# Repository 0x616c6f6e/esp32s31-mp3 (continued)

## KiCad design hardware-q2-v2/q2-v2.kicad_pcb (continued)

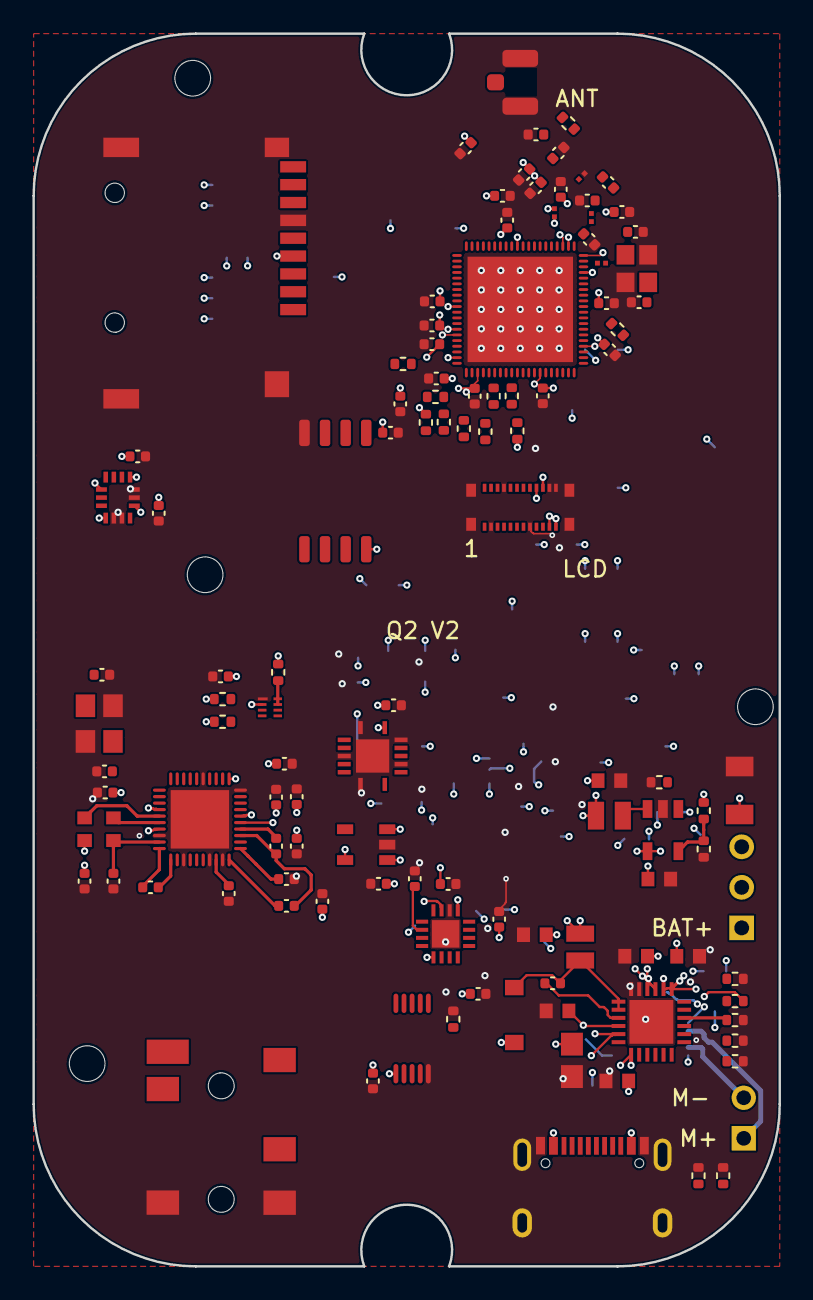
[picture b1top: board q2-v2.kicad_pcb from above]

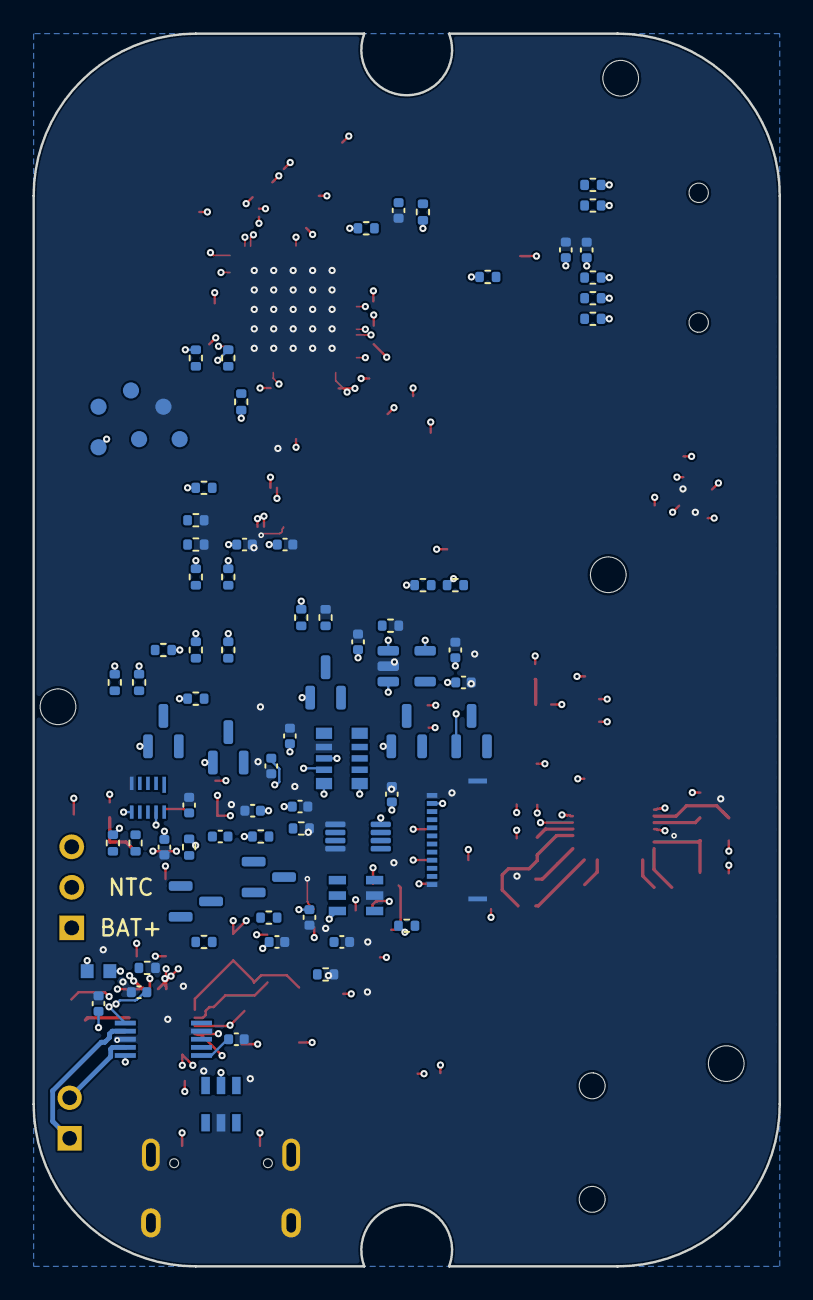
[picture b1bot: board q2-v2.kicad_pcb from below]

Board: 6 copper layers, 46.0 x 76.0 mm, 198 parts (83 on the bottom side), 144 nets.

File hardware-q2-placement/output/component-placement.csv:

Reference,Side,X_mm,Y_mm,Rotation_deg,Value,Locked
C1,B,126.25,90.25,0.0,10uF,False
C10,B,135.5,108.25,0.0,10uF,False
C11,B,144.25,111.25,90.0,47nF,False
C12,B,141.75,107.75,-90.0,10uF,False
C14,B,135.5,116.75,90.0,1uF,False
C15,B,133.5,110.25,0.0,10uF,False
C16,B,138.75,116.25,180.0,47uF,False
C17,F,106.5,108.25,180.0,2.2uF,False
C18,F,106.0,106.5,180.0,22uF,False
C19,F,103.5,106.0,90.0,2.2uF,False
C2,B,129.5,88.0,0.0,10uF,False
C20,F,109.5,109.75,0.0,2.2uF,False
C21,F,116.25,110.5,-90.0,2.2uF,False
C22,F,111.75,110.5,-90.0,2.2uF,False
C23,F,115.75,104.5,-90.0,2.2uF,False
C24,F,115.75,107.25,-90.0,2.2uF,False
C25,F,114.0,109.75,0.0,2.2uF,False
C26,F,117.25,105.0,90.0,4.7uF,False
C27,F,115.5,101.5,0.0,100nF,False
C28,B,108.5,105.0,0.0,100nF,False
C29,F,117.25,107.75,-90.0,100nF,False
C3,B,115.75,88.0,180.0,100nF,False
C30,F,124.0,99.0,90.0,1uF,False
C31,F,118.0,100.0,-90.0,1uF,False
C32,F,114.75,99.0,-90.0,10pF,False
C33,F,108.5,100.0,90.0,10pF,False
C34,F,105.5,95.25,-90.0,100nF,False
C35,F,118.25,90.75,180.0,100nF,False
C36,B,138.25,104.0,0.0,100nF,False
C37,B,133.75,93.75,-90.0,100nF,False
C38,B,131.25,97.0,0.0,100nF,False
C39,F,121.019,66.581,-90.0,1uF,False
C4,F,120.25,117.25,-90.0,1uF,False
C40,F,121.019,63.914,90.0,100nF,False
C41,F,119.749,63.914,90.0,1uF,False
C42,B,135.5,75.5,90.0,10uF,False
C43,B,139.75,99.25,90.0,220nF,False
C44,B,127.5,96.0,-90.0,100nF,False
C45,B,143.323,66.018,0.0,100nF,False
C46,B,137.608,62.081,0.0,100nF,False
C47,F,120.5,78.5,0.0,100nF,False
C48,F,115.25,78.0,-90.0,100nF,False
C49,B,119.574,63.935,-90.0,10uF,False
C5,F,120.25,113.75,90.0,1uF,False
C50,B,120.8615,63.93,-90.0,100nF,False
C53,F,140.0,92.5,-90.0,100nF,False
C54,F,138.5,92.5,-90.0,1uF,False
C55,B,131.0,75.75,90.0,10uF,False
C56,B,138.5,78.25,180.0,10uF,False
C57,B,138.25,76.25,180.0,10uF,False
C58,F,121.5,111.25,0.0,100nF,False
C6,F,141.75,86.5,90.0,100nF,False
C7,F,143.25,88.0,-90.0,100nF,False
C8,F,106.0,104.5,180.0,22uF,False
C9,B,142.75,115.75,0.0,4.7uF,False
CARD2,F,111.7,65.764,-90.0,TF PUSH,True
CN1,F,112.565,118.425,90.0,PJ-342B-TX-SMT,True
D1,F,135.5,115.75,0.0,USBLC6-2SC6,False
D2,B,142.25,112.25,90.0,B5817W,False
FPC2,B,140.148,69.4,90.0,2.09寸320*375高清R角方屏QSPI,True
H1,F,130.0,113.0,-90.0,BM02B-ACHSS-GAN-ETF,True
H2,F,142.0,109.0,-90.0,BM03B-ACHSS-GAN-ETF,True
L1,B,129.75,85.75,180.0,2.2uH,False
L2,B,139.0,108.0,0.0,2.2uH,False
L3,F,124.5,111.0,0.0,BLM18KG601SN1D,False
L4,B,133.25,75.75,-90.0,4.7uH,False
R1,B,144.0,106.5,90.0,10mΩ,False
R11,B,132.25,114.75,90.0,100K,False
R12,B,133.75,117.0,90.0,100K,False
R13,B,133.0,112.5,90.0,5K23,False
R14,B,131.0,110.25,-90.0,30K1,False
R17,F,109.0,92.5,90.0,200K,False
R18,F,107.0,93.0,180.0,10K,False
R19,F,104.0,95.25,90.0,10K,False
R2,B,141.0,103.5,180.0,1K,False
R20,B,141.594,62.85,0.0,10K,False
R21,B,139.25,97.25,180.0,100K,False
R22,B,136.0,104.0,180.0,100K,False
R25,B,141.594,64.376,0.0,10K,False
R26,F,109.25,94.75,-90.0,10K,False
R27,B,130.25,91.0,0.0,0/NC,False
R28,B,127.5,93.75,90.0,0/NC,False
R29,F,119.749,66.454,90.0,10K,False
R3,B,123.25,90.0,90.0,22K1,False
R30,F,109.75,96.75,180.0,10K,False
R31,F,132.25,117.75,0.0,5K1,False
R32,F,138.75,117.75,180.0,5K1,False
R33,B,139.75,101.5,90.0,1K,False
R34,B,141.5,105.0,180.0,0R/NC,False
R35,B,120.209,60.303,0.0,10K,False
R36,B,120.209,68.177,0.0,10K,False
R37,B,120.209,66.907,0.0,10K,False
R38,B,120.209,61.573,0.0,10K,False
R39,B,120.209,65.637,0.0,10K,False
R4,B,123.25,87.75,90.0,100K,False
R40,B,139.5,80.5,180.0,1R5,False
R41,B,131.5,81.0,90.0,100K,False
R42,F,141.75,91.25,90.0,10K,False
R43,B,133.75,114.75,90.0,10K,False
R44,F,125.75,117.5,-90.0,10K,False
R5,B,125.5,84.0,180.0,100K,False
R7,F,135.75,88.0,-90.0,10K,False
R8,F,141.75,88.75,90.0,10K,False
R9,B,134.5,112.5,90.0,700R,False
SCREW1,F,104.3,114.5,0.0,M2 clearance 2.2mm,True
SCREW2,F,111.573,84.3608,0.0,M2 clearance 2.2mm,True
SCREW4,F,145.5,92.5,0.0,M2 clearance 2.2mm,True
SCREW5,F,110.8085,53.7485,0.0,M2 clearance 2.2mm,True
U1,F,139.0,89.0,0.0,RX8130CE:BB,False
U11,F,123.0,115.5,0.0,DRV2605LDGSR,False
U12,B,130.5,94.0,-90.0,CH343P,False
U14,B,142.5,101.0,0.0,STC3115AIQT,False
U15,F,117.7,78.0,90.0,LSM6DS3TR-C,False
U16,B,134.56,79.559,180.0,PAM2804AAB010,False
U17,B,136.0,100.0,180.0,SGM7229YMS10G/TR,False
U2,F,111.7,105.69,0.0,CS43131-CNZ,False
U3,B,138.0,112.2,90.0,DSCB_BQ25895RTW,False
U4,B,126.0,87.0,90.0,TLV62568DBVR,False
U5,F,121.0,99.5,0.0,ME6211C18M5G-N,False
U6,B,116.5,91.0,-90.0,GEK100,False
U7,F,107.4,95.0,-90.0,PCA9306DQER,False
U8,F,117.0,94.0,-90.0,SN74LV4T125RGYR,False
U9,F,133.719,72.931,0.0,ESP32-S31-WROOM-3-N16R16V,True
USB1,F,135.449,121.946,0.0,TYPE-C 16PIN 2MD(073),True
X1,F,111.5,100.25,180.0,26MHz,False

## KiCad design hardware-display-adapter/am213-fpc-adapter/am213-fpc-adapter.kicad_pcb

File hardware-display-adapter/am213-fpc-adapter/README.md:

# AM213 转接板 A

打开 `am213-fpc-adapter.kicad_pro`。现为已完成原理图和布线的电气工程，取代旧机械占位版本。

- 原理图、PCB：同名 `.kicad_sch`、`.kicad_pcb`
- 自带库：`Adapter.kicad_sym`、`Adapter.pretty`、`models3d`
- 最新装配副本：`models3d/Q2_L_AM213_Completed_Adapter.FCStd`
- 检查、BOM、预览及制造审核包：`output/`

采用屏厂 3.3 V 直接接线参考；17×22 mm 元件岛、70 mm 左出尾巴；J2 局部 **(3,12)**、1 脚左上。R10/R11 不装。ERC/DRC、未连接和原理图一致性问题均为 0。

详见[接线与坐标](../fpc-layout-guide.md)、[电气依据](../README.md)、[制造说明](FABRICATION.md)。先审核柔性叠层、补强、0.15 mm 小孔及金手指工艺，再做样板；尚未实物插合和点亮。

`Adapter_Placement.pretty`、旧 `placement-preview.*` 及 `models3d/Q2_L_BTB_Fit_Review.FCStd` 为历史阶段文件。

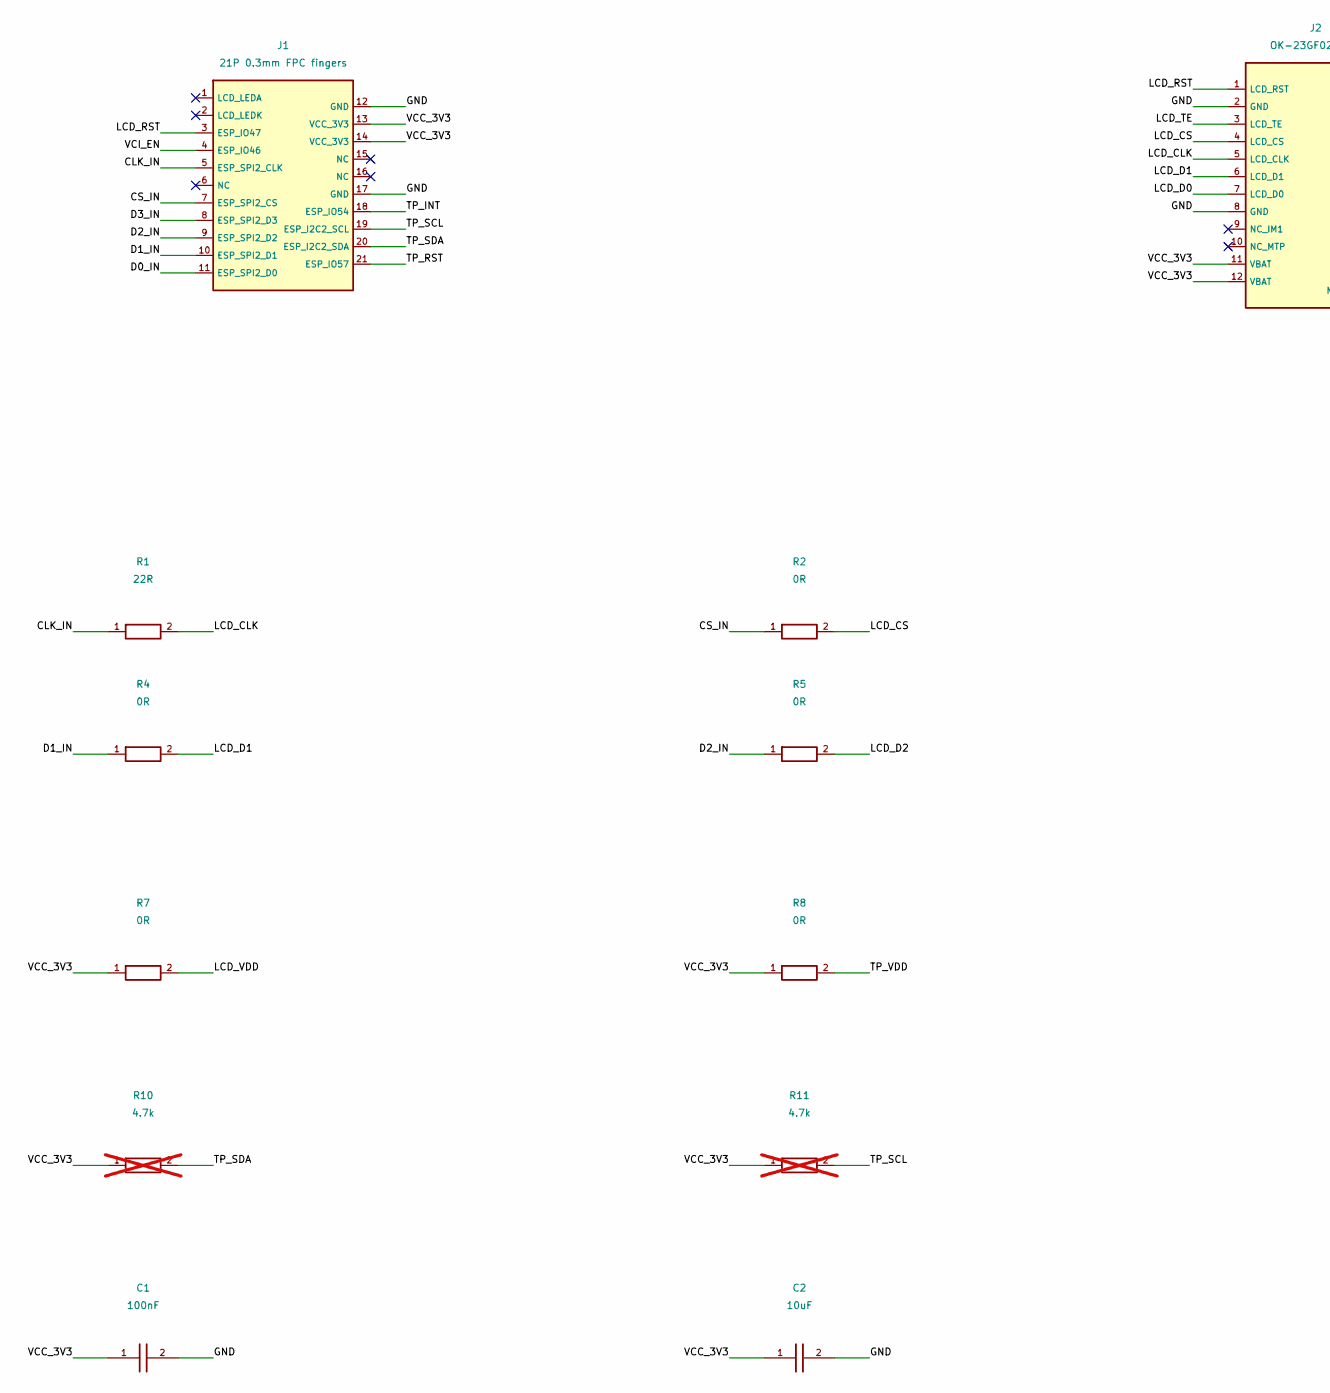
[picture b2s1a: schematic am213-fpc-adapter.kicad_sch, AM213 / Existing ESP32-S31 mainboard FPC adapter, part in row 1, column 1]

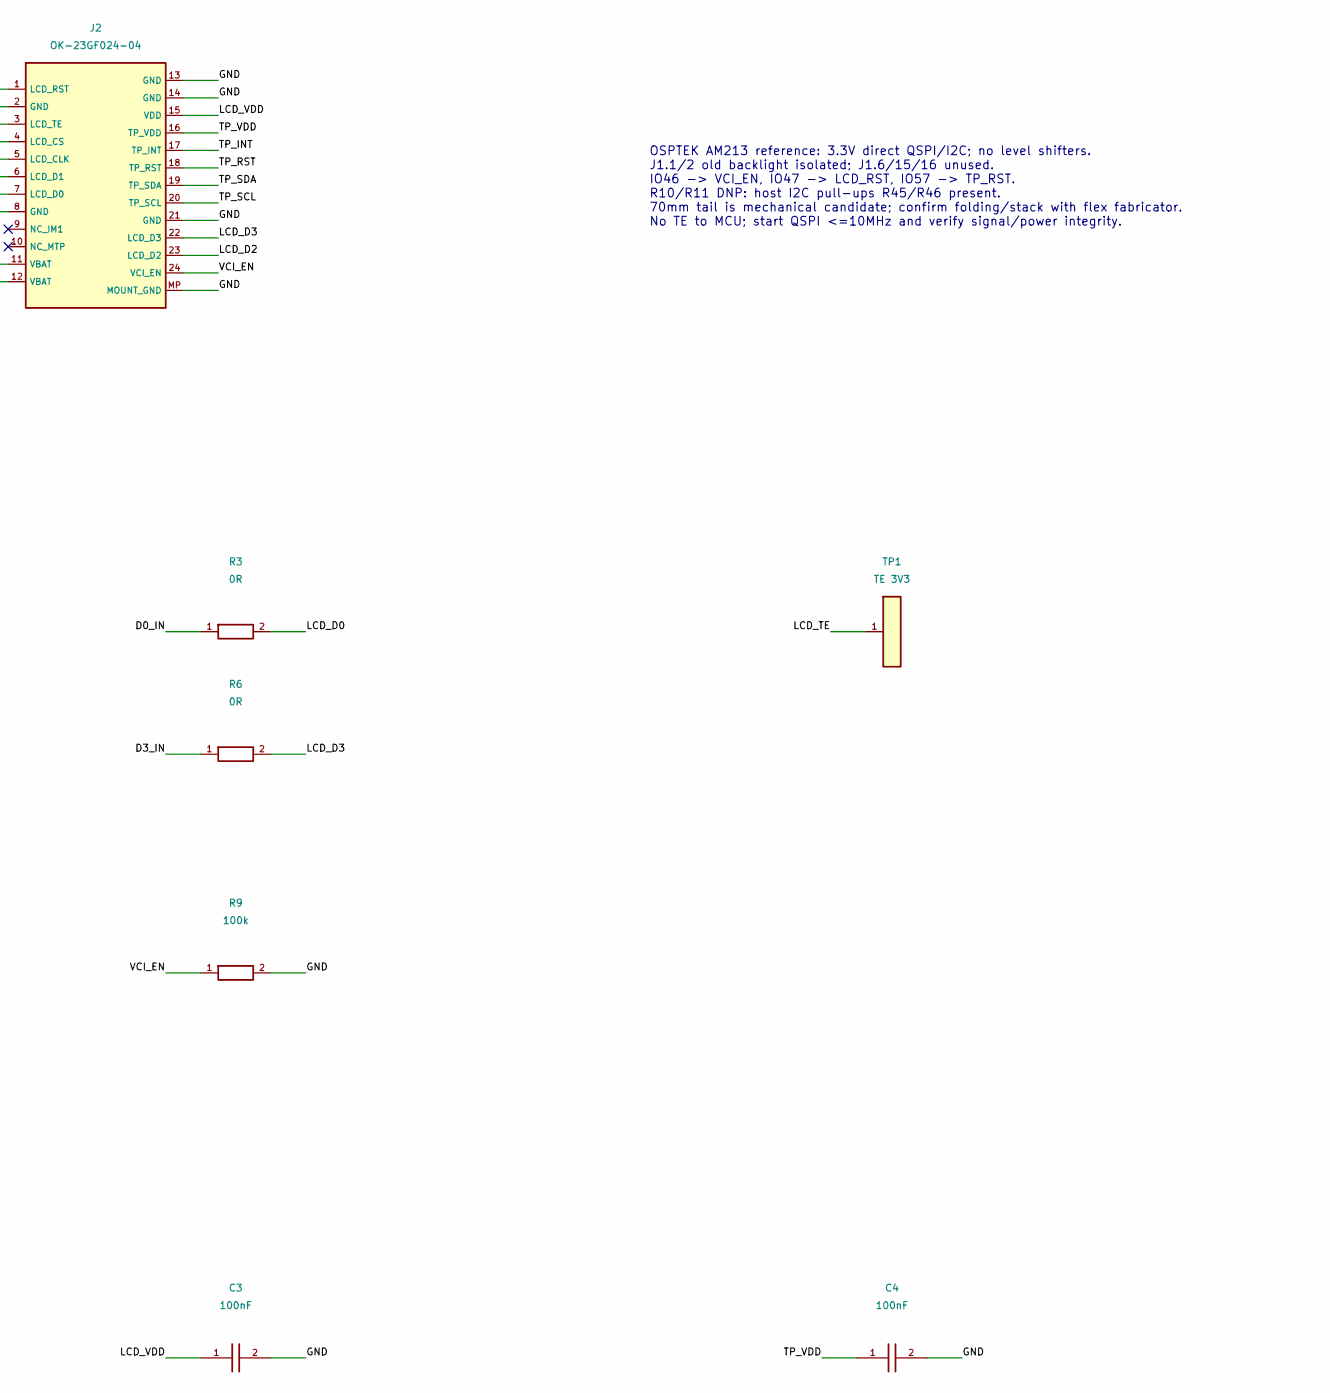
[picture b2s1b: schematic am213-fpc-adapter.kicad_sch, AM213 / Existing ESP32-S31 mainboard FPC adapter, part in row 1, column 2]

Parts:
C1, C3, C4: 100nF; C0402
C2: 10uF; C0603
J1: 21P 0.3mm FPC fingers; FPC21_Fingers
J2: OK-23GF024-04; OK23GF024
R1: 22R; R0402
R2, R3, R4, R5, R6, R7, R8: 0R; R0402
R9: 100k; R0402
R10, R11: 4.7k; R0402; not fitted
TP1: TE 3V3; TP

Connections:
/CLK_IN: J1.5 (ESP_SPI2_CLK), R1.1
/CS_IN: J1.7 (ESP_SPI2_CS), R2.1
/D0_IN: J1.11 (ESP_SPI2_D0), R3.1
/D1_IN: J1.10 (ESP_SPI2_D1), R4.1
/D2_IN: J1.9 (ESP_SPI2_D2), R5.1
/D3_IN: J1.8 (ESP_SPI2_D3), R6.1
/GND: C1.2, C2.2, C3.2, C4.2, J1.12 (GND), J1.17 (GND), J2.2 (GND), J2.8 (GND), J2.13 (GND), J2.14 (GND), J2.21 (GND), J2.MP (MOUNT_GND), R9.2
/LCD_CLK: J2.5 (LCD_CLK), R1.2
/LCD_CS: J2.4 (LCD_CS), R2.2
/LCD_D0: J2.7 (LCD_D0), R3.2
/LCD_D1: J2.6 (LCD_D1), R4.2
/LCD_D2: J2.23 (LCD_D2), R5.2
/LCD_D3: J2.22 (LCD_D3), R6.2
/LCD_RST: J1.3 (ESP_IO47), J2.1 (LCD_RST)
/LCD_TE: J2.3 (LCD_TE), TP1.1
/LCD_VDD: C3.1, J2.15 (VDD), R7.2
/TP_INT: J1.18 (ESP_IO54), J2.17 (TP_INT)
/TP_RST: J1.21 (ESP_IO57), J2.18 (TP_RST)
/TP_SCL: J1.19 (ESP_I2C2_SCL), J2.20 (TP_SCL), R11.2
/TP_SDA: J1.20 (ESP_I2C2_SDA), J2.19 (TP_SDA), R10.2
/TP_VDD: C4.1, J2.16 (TP_VDD), R8.2
/VCC_3V3: C1.1, C2.1, J1.13 (VCC_3V3), J1.14 (VCC_3V3), J2.11 (VBAT), J2.12 (VBAT), R7.1, R8.1, R10.1, R11.1
/VCI_EN: J1.4 (ESP_IO46), J2.24 (VCI_EN), R9.1

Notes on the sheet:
OSPTEK AM213 reference: 3.3V direct QSPI/I2C; no level shifters. J1.1/2 old backlight isolated; J1.6/15/16 unused. IO46 -> VCI_EN, IO47 -> LCD_RST, IO57 -> TP_RST. R10/R11 DNP: host I2C pull-ups R45/R46 present. 70mm tail is mechanical candidate; confirm folding/stack with flex fabricator. No TE to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

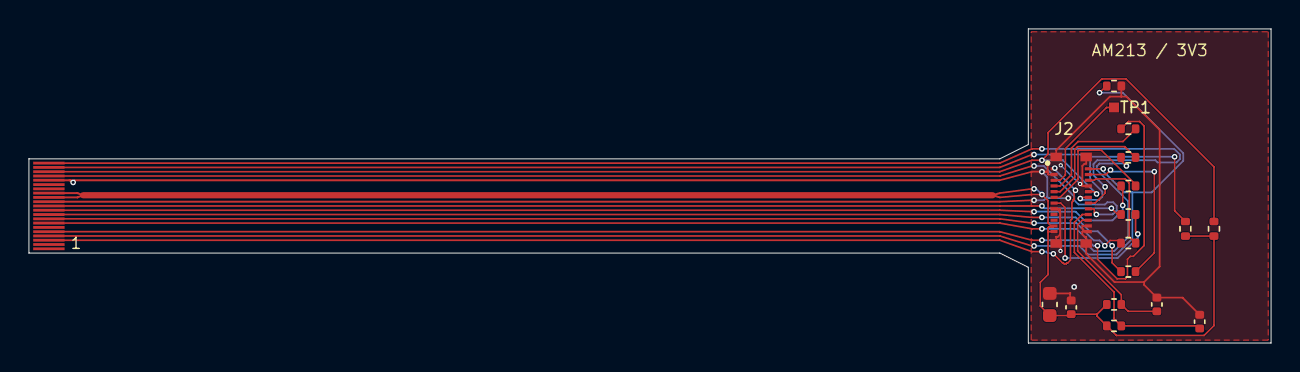
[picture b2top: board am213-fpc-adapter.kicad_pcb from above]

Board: 2 copper layers, 87.0 x 22.0 mm, 18 parts (0 on the bottom side), 23 nets.

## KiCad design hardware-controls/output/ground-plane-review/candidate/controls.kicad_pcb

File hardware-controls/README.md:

# 滑环与按键小板 C：CH32V006

采用 **CH32V006F8U6** 替换 AT42QT2120-MMHR 和 TCA6408A，由一颗 MCU 处理三电极滑环、四个机械按键，并作为 I²C 从机向主板报告。POWER 保持独立、10 kΩ 上拉、按下接地。

这是需要配套固件和实物调参的新硬件版本，不能直接沿用旧 AT42 的驱动或生产文件。

KiCad 10.0.4 检查结果：ERC 0、DRC 0、未连接项 0、原理图一致性问题 0。板上共有 439 段走线和 62 个过孔。双面 GND 铺铜避开触摸电极及其背面（外扩约 0.8 mm），并避开三路采样走线（铜边外扩约 0.5 mm）；这些余量仍需实物验证。

新版文件：[Gerber 生产包](output/controls-ch32v006-jlcpcb-20260922-101316-gerbers.zip)、[BOM](output/controls-ch32v006-bom.csv)、[装配 STEP](output/controls-ch32v006.step)、[背面预览](output/ch32v006-review/back.png)。BOM 由当前原理图导出，共 10 类、23 个装配元件，尚未匹配嘉立创 SMT 料号。

## 工程与机械接口

- KiCad 工程：`controls.kicad_pro`，原理图、PCB、本地符号库、封装库与模型一起使用。
- 双层 FR-4，板厚 0.8 mm，44 × 34 mm，原 R10 板框。
- 五个按键、四个安装孔、三电极滑环 E1、FPC J1 的位置与方向保持原样。
- 电极仍为三组插值电极，外径 31 mm、内径 15 mm；不改变前面板外观。
- 新 MCU 及阻容位于背面。J2 为四个裸焊盘，不安装插针，不增加连接器高度。
- 已添加名义尺寸的 CH32V006 QFN20 STEP 模型。本版 23 个元件已导入 [I 版装配优化工程](../mechanical/enclosure-final-i/README.md)，最新工程为 `mechanical/enclosure-final-i/Q2_I_Serviceable_Assembly.FCStd`。小板采用三颗 M1.6 × 2 mm（头下长度）薄头螺钉、三片 0.3 mm 平垫及右侧限位台；右上原固定柱封闭不装螺钉，避开 FFC。G/H 复合实体检查曾漏报该处干涉，使用 I 版检查和打印文件。

J1：1 GND、2 +3V3、3 SDA、4 SCL、5 INT_N、6 RESET_N、7～10 NC、11 KEY_POWER、12 GND；固定焊盘 13、14 接地。供电与信号电平为 3.3 V。

## 采购与装配变化

| 位号 | C 版器件/数值 | 数量 | 说明 |
|---|---|---:|---|
| U1 | CH32V006F8U6 | 1 | QFN20，3×3 mm，0.4 mm 脚距，EP 1.9×1.9 mm |
| J1 | HC-FPC-05-10-12RLTAG | 1 | 原 12 pin、0.5 mm FPC 连接器 |
| SW1～SW5 | SKSWCEE010 | 5 | 原机械开关 |
| R1～R3 | 1 kΩ，0402 | 3 | 触摸采样串阻，需实物调参 |
| R4、R5 | 4.7 kΩ，0402 | 2 | I²C 上拉 |
| R6、R7、R14 | 10 kΩ，0402 | 3 | INT、RESET、POWER 上拉 |
| R8 | 0 Ω，0402 | 1 | MCU 电源连接，不能装旧 22 Ω |
| R9～R12 | 47 kΩ，0402 | 4 | 四个普通键的 GPIO 上拉 |
| C1、C3 | 100 nF，0402，X7R，≥10 V | 2 | MCU 去耦、复位 RC |
| C2 | 1 µF，0402，X5R/X7R，≥10 V | 1 | MCU 电源去耦 |

单板 23 个采购/装配元件。J2、E1、H1～H4 为 PCB 自带焊盘、电极及安装孔，不采购。U2、R13、C4 已移除；C3 现在用于复位，不能按旧版位置和功能装配。型号后缀及封装必须核对，TSSOP20 的 CH32V006F8P6 不能替代此 QFN20 焊盘。

## 固件

见 [CH32V006-interface.md](CH32V006-interface.md)：完整引脚分配、SDI 下载、PD7 硬件复位配置，以及拟定的 I²C 寄存器协议。地址暂定 0x1C，寄存器与 AT42QT2120 不兼容。本次没有交付可烧录固件；官方 TouchKey 示例也不能原样烧录到此板。

打样后要在最终盖板下标定三路触摸基线、阈值、零位、转动方向与跨零连续性，并验证充电/音频干扰、按键消抖、待机电流、复位和再次下载能力。

## 检查与历史文件

本次备份、原生 ERC/DRC 报告、机械接口比较和预览位于 `output/ch32v006-review/`，以其中的 final 报告和 `validation.json` 为准。历史生成脚本可能仍包含 B 版芯片和旧镜像坐标，不要直接运行旧 `build_design.py` 或 `build_fit.py` 覆盖当前工程。

2026-09-22 10:13:16 批次已从用户调整走线后的 C 版导出 Gerber 生产包（源 PCB 保存时间为 10:13:08），包含九个图层、独立 PTH/NPTH 钻孔、Gerber Job 和加工说明。下单参数：双层 FR-4、44 × 34 mm、板厚 0.8 mm、外层铜厚 1 oz。62 个 Ø0.30 mm 镀铜过孔及四个 Ø1.80 mm 非金属化安装孔已与 PCB 核对；顶面触摸电极保留阻焊覆盖。导出前原生 DRC、未连接项和原理图一致性问题均为 0；文件校验和及检查记录见 `output/ch32v006-gerber-review-20260922-101316/manifest.json`。

**旧 `controls-jlcpcb-20260922-no-tp-gerbers.zip`、旧 BOM、`fabrication/` 和历史 STEP 是 AT42/TCA 版本，全部不适用于 C 版。** 旧 README 与原始工程在 `output/ch32v006-review/before/` 保留。

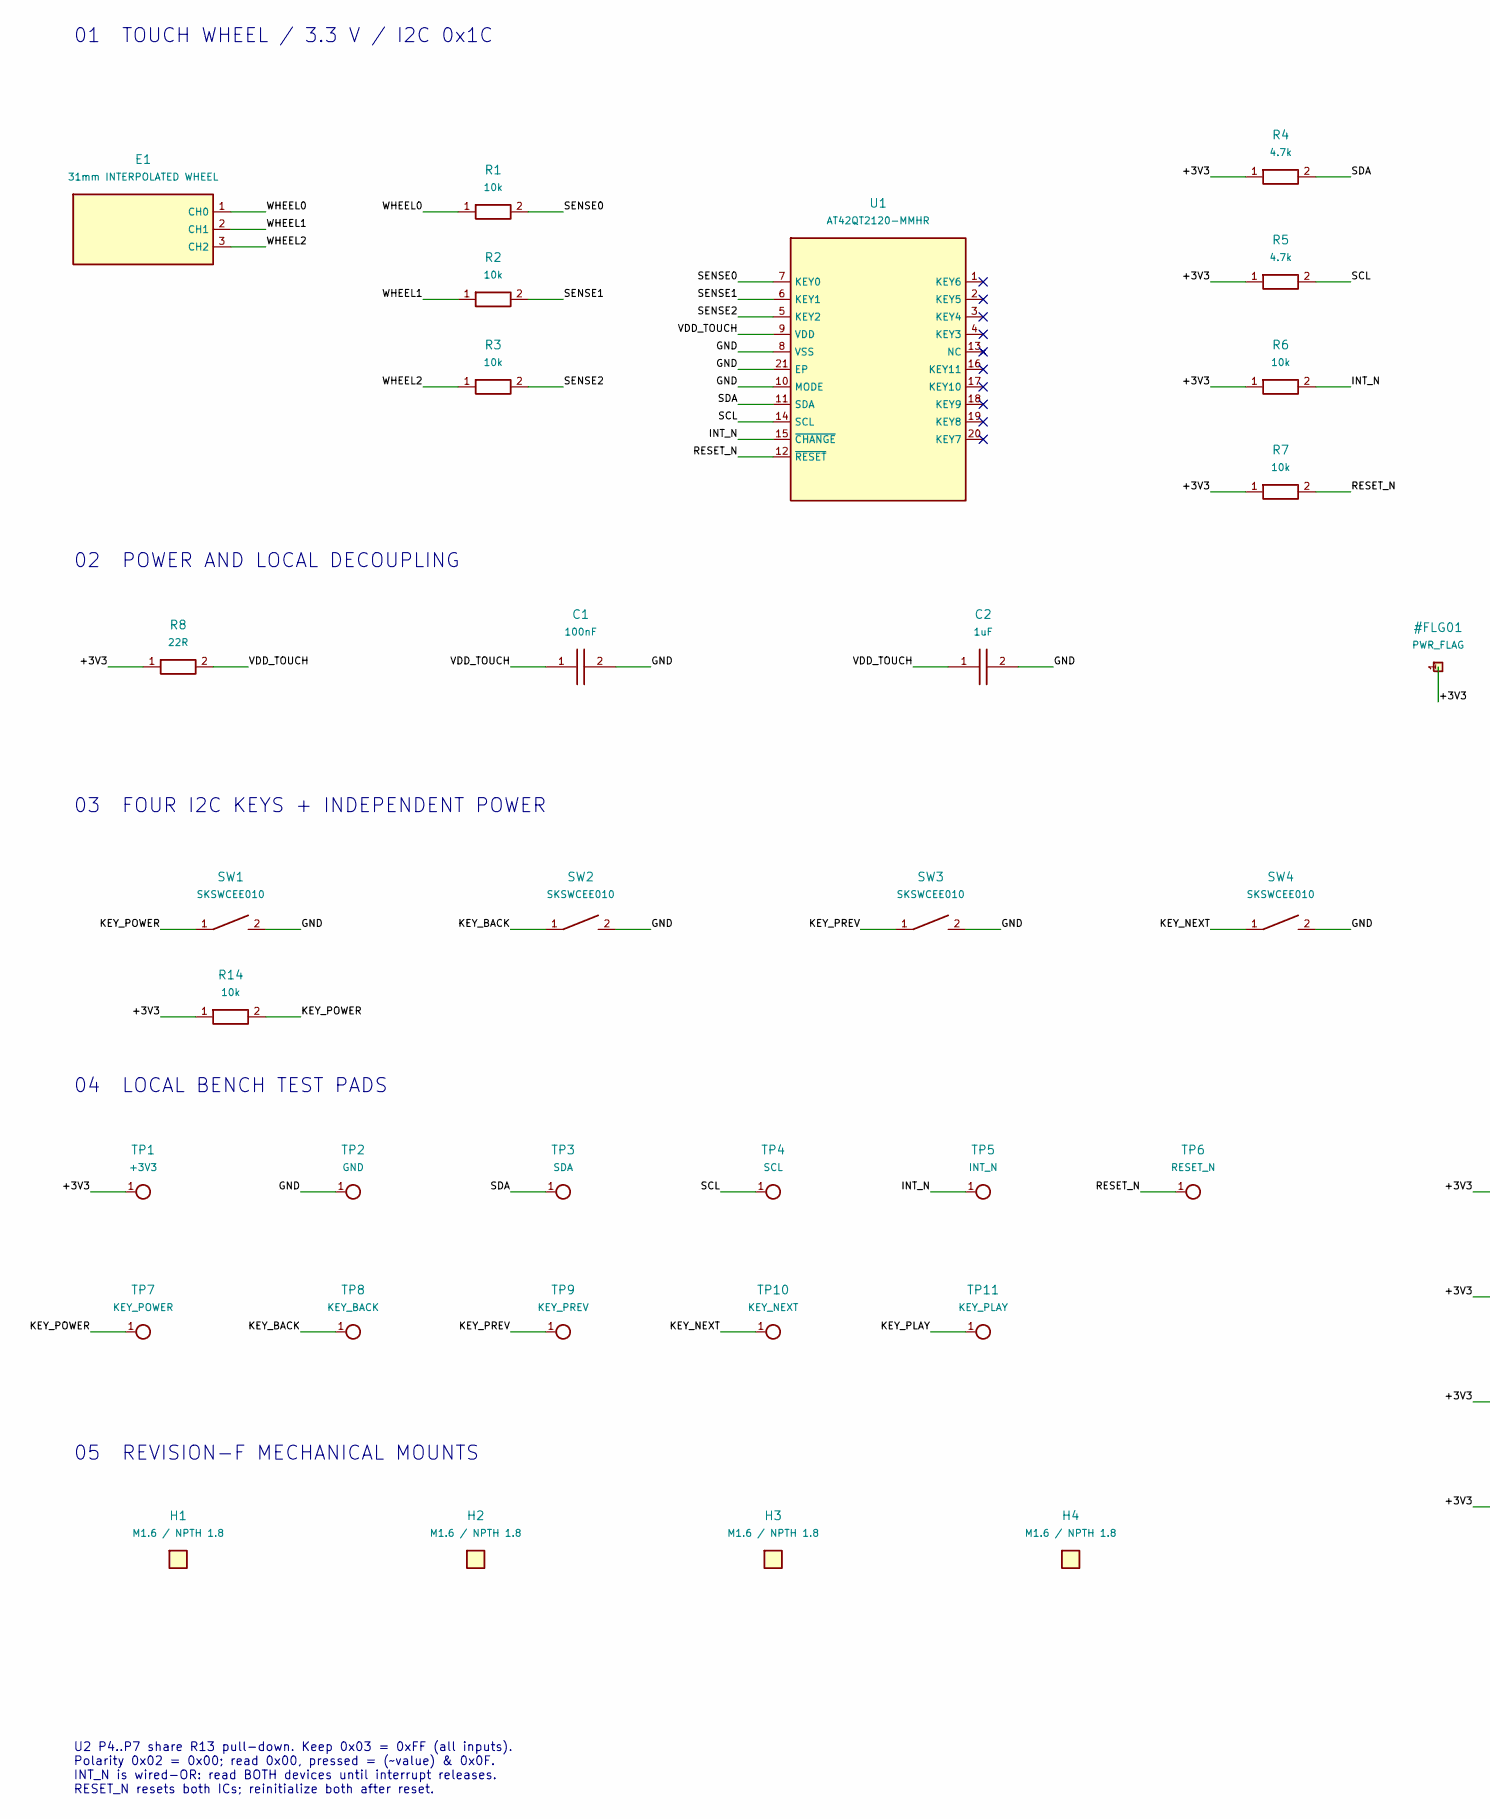
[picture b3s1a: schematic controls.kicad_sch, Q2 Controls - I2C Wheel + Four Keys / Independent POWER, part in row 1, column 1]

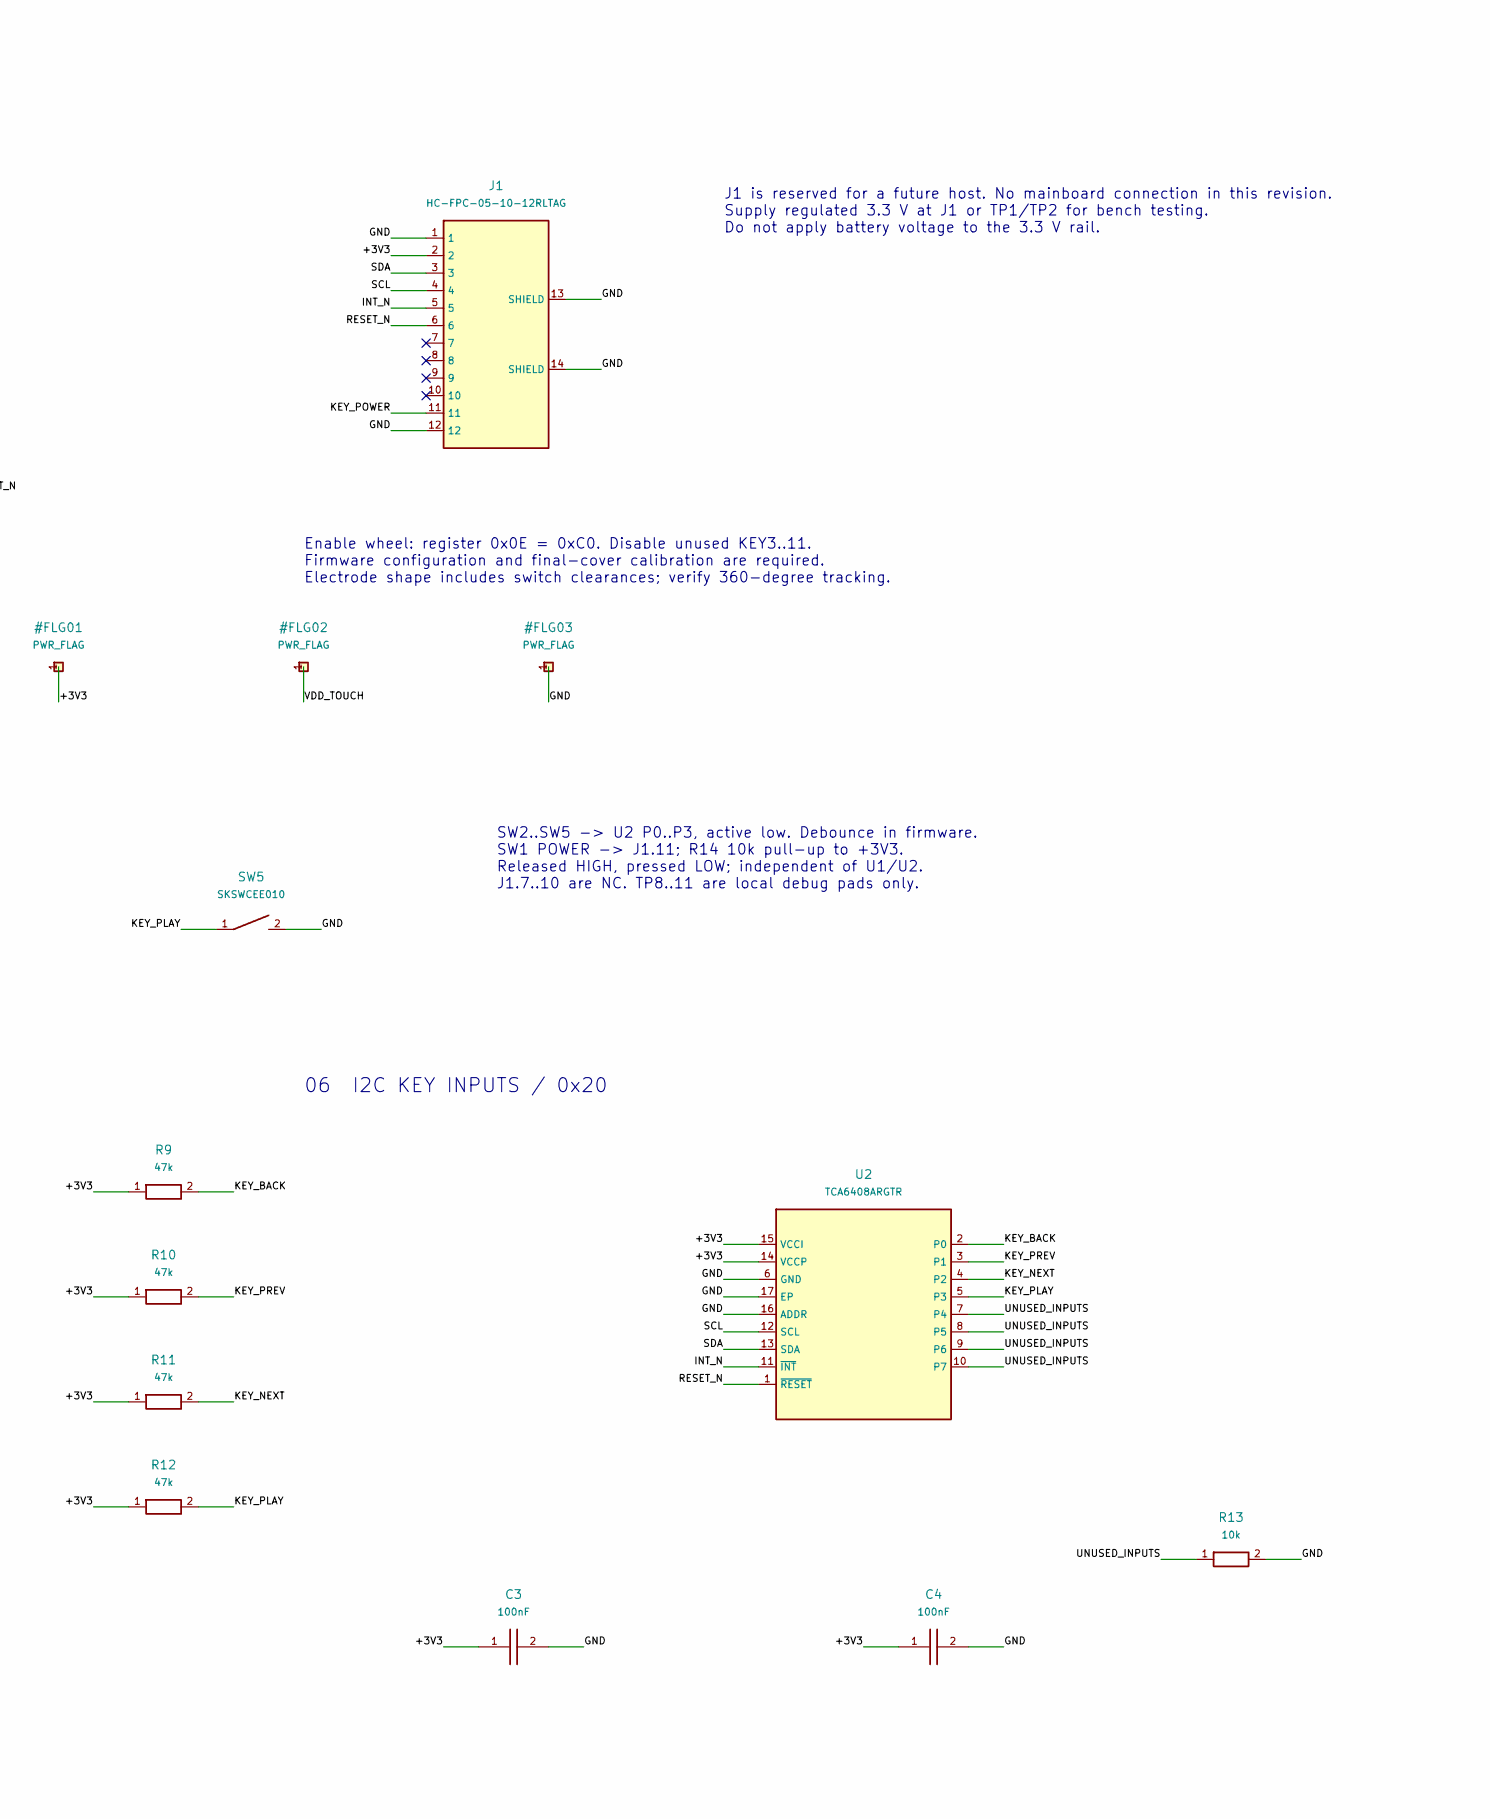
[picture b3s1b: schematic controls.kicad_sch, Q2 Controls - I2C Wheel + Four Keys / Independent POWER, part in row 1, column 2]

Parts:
C1, C3, C4: 100nF; C0402
C2: 1uF; C0402
E1: 31mm INTERPOLATED WHEEL; Wheel_D31
H1, H2, H3, H4: M1.6 / NPTH 1.8; Mount_1.8
J1: HC-FPC-05-10-12RLTAG; HCTL_FPC12
R1, R2, R3, R6, R7, R13, R14: 10k; R0402
R4, R5: 4.7k; R0402
R8: 22R; R0402
R9, R10, R11, R12: 47k; R0402
SW1, SW2, SW3, SW4, SW5: SKSWCEE010; SKSW_3x2
TP1: +3V3; TestPad
TP2: GND; TestPad
TP3: SDA; TestPad
TP4: SCL; TestPad
TP5: INT_N; TestPad
TP6: RESET_N; TestPad
TP7: KEY_POWER; TestPad
TP8: KEY_BACK; TestPad
TP9: KEY_PREV; TestPad
TP10: KEY_NEXT; TestPad
TP11: KEY_PLAY; TestPad
U1: AT42QT2120-MMHR; QT2120_VQFN20
U2: TCA6408ARGTR; TCA6408A_VQFN16

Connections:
/+3V3: C3.1, C4.1, J1.2, R4.1, R5.1, R6.1, R7.1, R8.1, R9.1, R10.1, R11.1, R12.1, R14.1, TP1.1, U2.14 (VCCP), U2.15 (VCCI)
/GND: C1.2, C2.2, C3.2, C4.2, J1.1, J1.12, J1.13 (SHIELD), J1.14 (SHIELD), R13.2, SW1.2, SW2.2, SW3.2, SW4.2, SW5.2, TP2.1, U1.8 (VSS), U1.10 (MODE), U1.21 (EP), U2.6 (GND), U2.16 (ADDR), U2.17 (EP)
/INT_N: J1.5, R6.2, TP5.1, U1.15 (~CHANGE), U2.11 (~INT)
/KEY_BACK: R9.2, SW2.1, TP8.1, U2.2 (P0)
/KEY_NEXT: R11.2, SW4.1, TP10.1, U2.4 (P2)
/KEY_PLAY: R12.2, SW5.1, TP11.1, U2.5 (P3)
/KEY_POWER: J1.11, R14.2, SW1.1, TP7.1
/KEY_PREV: R10.2, SW3.1, TP9.1, U2.3 (P1)
/RESET_N: J1.6, R7.2, TP6.1, U1.12 (~RESET), U2.1 (~RESET)
/SCL: J1.4, R5.2, TP4.1, U1.14 (SCL), U2.12 (SCL)
/SDA: J1.3, R4.2, TP3.1, U1.11 (SDA), U2.13 (SDA)
/SENSE0: R1.2, U1.7 (KEY0)
/SENSE1: R2.2, U1.6 (KEY1)
/SENSE2: R3.2, U1.5 (KEY2)
/UNUSED_INPUTS: R13.1, U2.7 (P4), U2.8 (P5), U2.9 (P6), U2.10 (P7)
/VDD_TOUCH: C1.1, C2.1, R8.2, U1.9 (VDD)
/WHEEL0: E1.1 (CH0), R1.1
/WHEEL1: E1.2 (CH1), R2.1
/WHEEL2: E1.3 (CH2), R3.1

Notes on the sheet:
01 TOUCH WHEEL / 3.3 V / I2C 0x1C
02 POWER AND LOCAL DECOUPLING
03 FOUR I2C KEYS + INDEPENDENT POWER
04 LOCAL BENCH TEST PADS
05 REVISION-F MECHANICAL MOUNTS
06 I2C KEY INPUTS / 0x20
J1 is reserved for a future host. No mainboard connection in this revision. Supply regulated 3.3 V at J1 or TP1/TP2 for bench testing. Do not apply battery voltage to the 3.3 V rail.
SW2..SW5 -> U2 P0..P3, active low. Debounce in firmware. SW1 POWER -> J1.11; R14 10k pull-up to +3V3. Released HIGH, pressed LOW; independent of U1/U2. J1.7..10 are NC. TP8..11 are local debug pads only.
Enable wheel: register 0x0E = 0xC0. Disable unused KEY3..11. Firmware configuration and final-cover calibration are required. Electrode shape includes switch clearances; verify 360-degree tracking.
U2 P4..P7 share R13 pull-down. Keep 0x03 = 0xFF (all inputs). Polarity 0x02 = 0x00; read 0x00, pressed = (~value) & 0x0F. INT_N is wired-OR: read BOTH devices until interrupt releases. RESET_N resets both ICs; reinitialize both after reset.

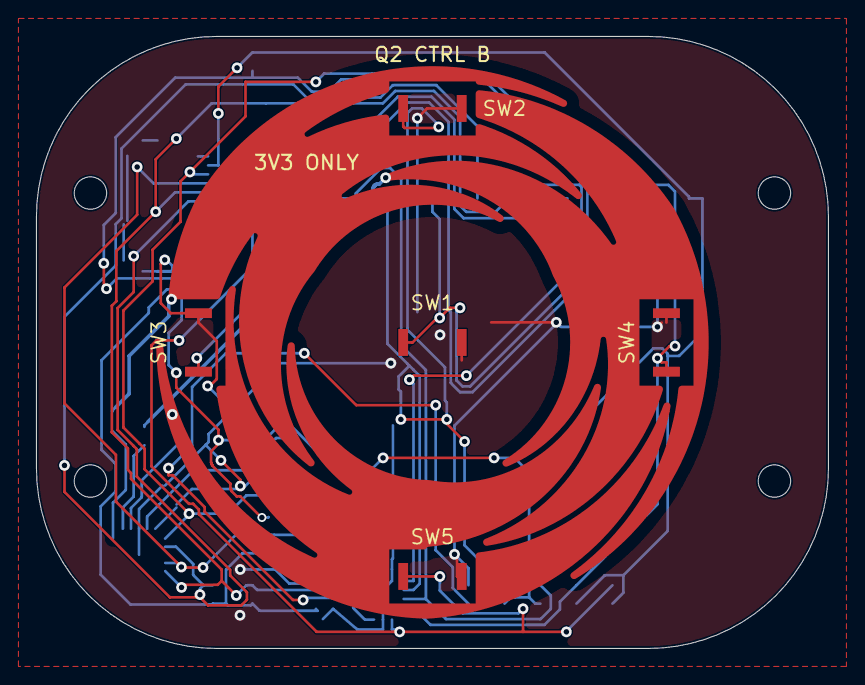
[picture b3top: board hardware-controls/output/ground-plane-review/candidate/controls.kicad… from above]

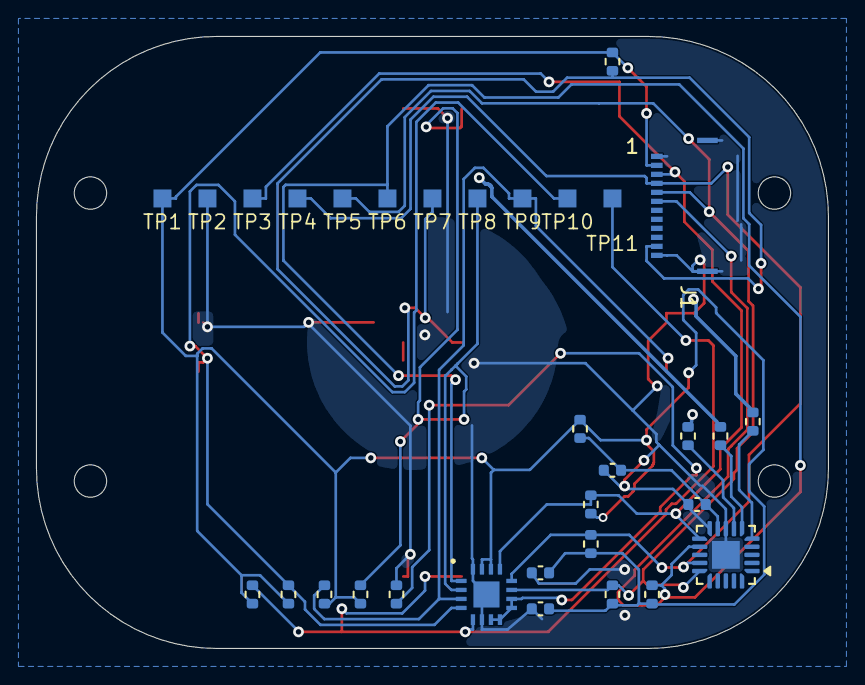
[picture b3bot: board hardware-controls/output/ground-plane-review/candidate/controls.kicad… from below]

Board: 2 copper layers, 44.0 x 34.0 mm, 42 parts (32 on the bottom side), 19 nets.

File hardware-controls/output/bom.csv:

Reference,Value,Footprint,Description,Datasheet
U1,AT42QT2120-MMHR,QT2120_VQFN20,3-channel wheel / I2C address 0x1C,https://ww1.microchip.com/downloads/en/devicedoc/doc9634.pdf
R1,10k,R0402,1% 0402 electrode series resistor,
R2,10k,R0402,1% 0402 electrode series resistor,
R3,10k,R0402,1% 0402 electrode series resistor,
R4,4.7k,R0402,Host-side 3.3 V pull-up; remove R4/R5 if host already supplies adequate I2C pull-ups,
R5,4.7k,R0402,Host-side 3.3 V pull-up; remove R4/R5 if host already supplies adequate I2C pull-ups,
R6,10k,R0402,Host-side 3.3 V pull-up; remove R4/R5 if host already supplies adequate I2C pull-ups,
R7,10k,R0402,Host-side 3.3 V pull-up; remove R4/R5 if host already supplies adequate I2C pull-ups,
R8,22R,R0402,Low-current RC supply filter,
C1,100nF,C0402,"X7R 10 V, close to U1 VDD",
C2,1uF,C0402,X5R/X7R 10 V reservoir,
SW1,SKSWCEE010,SKSW_3x2,POWER / independent active-low key; local 10k pull-up to +3V3,https://tech.alpsalpine.com/cms.media/product_catalog_ta_02_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
SW2,SKSWCEE010,SKSW_3x2,BACK / active-low TCA6408A input; local 47k pull-up; firmware debounce required,https://tech.alpsalpine.com/cms.media/product_catalog_ta_02_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
SW3,SKSWCEE010,SKSW_3x2,PREV / active-low TCA6408A input; local 47k pull-up; firmware debounce required,https://tech.alpsalpine.com/cms.media/product_catalog_ta_02_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
SW4,SKSWCEE010,SKSW_3x2,NEXT / active-low TCA6408A input; local 47k pull-up; firmware debounce required,https://tech.alpsalpine.com/cms.media/product_catalog_ta_02_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
SW5,SKSWCEE010,SKSW_3x2,PLAY / active-low TCA6408A input; local 47k pull-up; firmware debounce required,https://tech.alpsalpine.com/cms.media/product_catalog_ta_02_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
J1,HC-FPC-05-10-12RLTAG,HCTL_FPC12,"12 pin, 0.5 pitch, 0.3 FFC; tabs 13/14 GND; pins 7-10 NC; aligned with mainboard FPC1",https://atta.szlcsc.com/upload/public/pdf/source/20221027/B2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
R14,10k,R0402,"1% 0402 independent POWER pull-up; released high, pressed low",
U2,TCA6408ARGTR,TCA6408A_VQFN16,"I2C 0x20; P0..P3 four keys; P4..P7 common pull-down, KEEP AS INPUTS",https://www.ti.com/lit/ds/symlink/tca6408a.pdf
R13,10k,R0402,Shared pull-down for unused P4..P7; keep all four ports as inputs,
R9,47k,R0402,1% 0402 local active-low key pull-up,
R10,47k,R0402,1% 0402 local active-low key pull-up,
R11,47k,R0402,1% 0402 local active-low key pull-up,
R12,47k,R0402,1% 0402 local active-low key pull-up,
C3,100nF,C0402,X7R 10 V; U2 VCCI/VCCP bypass; both supplies on same 3.3 V rail,
C4,100nF,C0402,X7R 10 V; U2 VCCI/VCCP bypass; both supplies on same 3.3 V rail,
